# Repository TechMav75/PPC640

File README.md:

# Replacement keyboard controller for an Amstrad PPC640 luggable

The Keyboard Controller directory contain info on converting the existing keyboard to talk USB for use with a modern system. Gerber and schematic files are available in the directory also.

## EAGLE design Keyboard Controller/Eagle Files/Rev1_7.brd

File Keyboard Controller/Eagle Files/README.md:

# Eagle Files

The schematic and board files were created in Eagle v9.0.1

The Gerber files are generated and named for use with http://www.dirtypcbs.com

The board measures out to 4cm x 5.5cm. Can't get it any smaller because of the Teensy++ board.
You will have to use the 10cm x 10cm option, but you can get the proto-pack for $25 shipped

If ANYONE else wants to do the same type of conversion, I have spare boards I'd be will to part with for the cost of shipping. The protopack I ordered came with 12 boards.

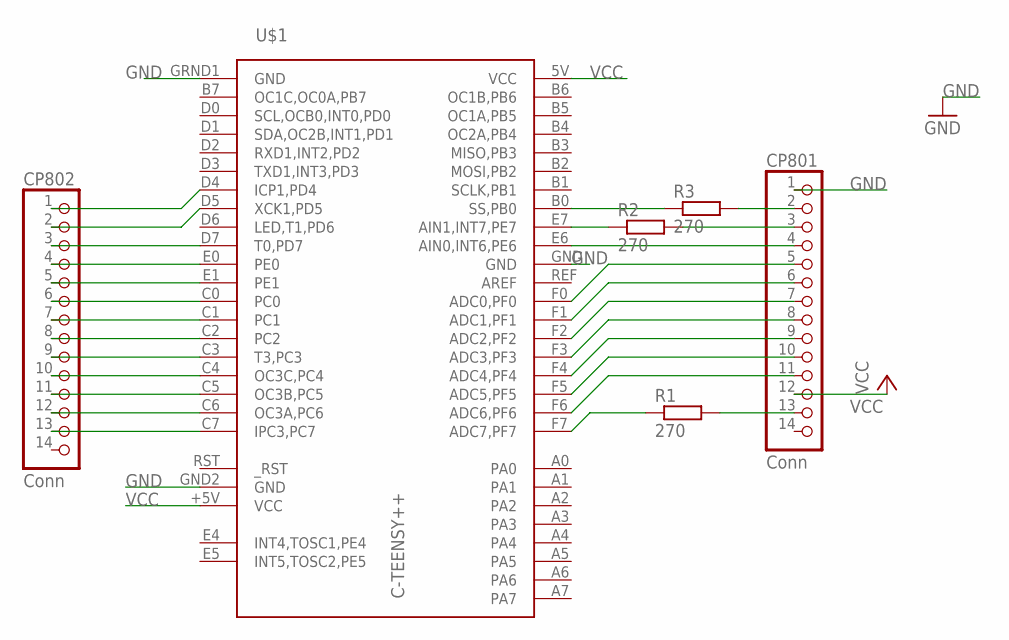
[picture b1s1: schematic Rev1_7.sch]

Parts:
CP801, CP802: Conn; 1X14
R1, R2, R3: 270; R0805
U$1: C-TEENSY++; TEENSY++

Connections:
GND: CP801.1, U$1.GND, U$1.GND2 (GND), U$1.GRND1 (GND)
unnamed: CP801.11, U$1.F6 (ADC6,PF6)
unnamed: CP802.13, U$1.C7 (IPC3,PC7)
unnamed: CP801.10, U$1.F5 (ADC5,PF5)
unnamed: CP801.9, U$1.F4 (ADC4,PF4)
unnamed: CP801.8, U$1.F3 (ADC3,PF3)
unnamed: CP801.7, U$1.F2 (ADC2,PF2)
unnamed: CP801.6, U$1.F1 (ADC1,PF1)
unnamed: CP801.5, U$1.F0 (ADC0,PF0)
unnamed: CP801.4, U$1.E6 (AIN0,INT6,PE6)
unnamed: CP802.12, U$1.C6 (OC3A,PC6)
unnamed: CP802.11, U$1.C5 (OC3B,PC5)
unnamed: CP802.10, U$1.C4 (OC3C,PC4)
unnamed: CP802.9, U$1.C3 (T3,PC3)
unnamed: CP802.8, U$1.C2
unnamed: CP802.7, U$1.C1
unnamed: CP802.6, U$1.C0
unnamed: CP802.5, U$1.E1
unnamed: CP802.4, U$1.E0
unnamed: CP802.3, U$1.D7 (T0,PD7)
unnamed: CP802.2, U$1.D5 (XCK1,PD5)
unnamed: CP802.1, U$1.D4 (ICP1,PD4)
unnamed: CP801.3, R2.2
unnamed: R2.1, U$1.E7 (AIN1,INT7,PE7)
unnamed: R3.1, U$1.B0 (SS,PB0)
unnamed: CP801.2, R3.2
unnamed: R1.1, U$1.F7 (ADC7,PF7)
unnamed: CP801.13, R1.2
VCC: CP801.12, U$1.5V (VCC), U$1.+5V (VCC)

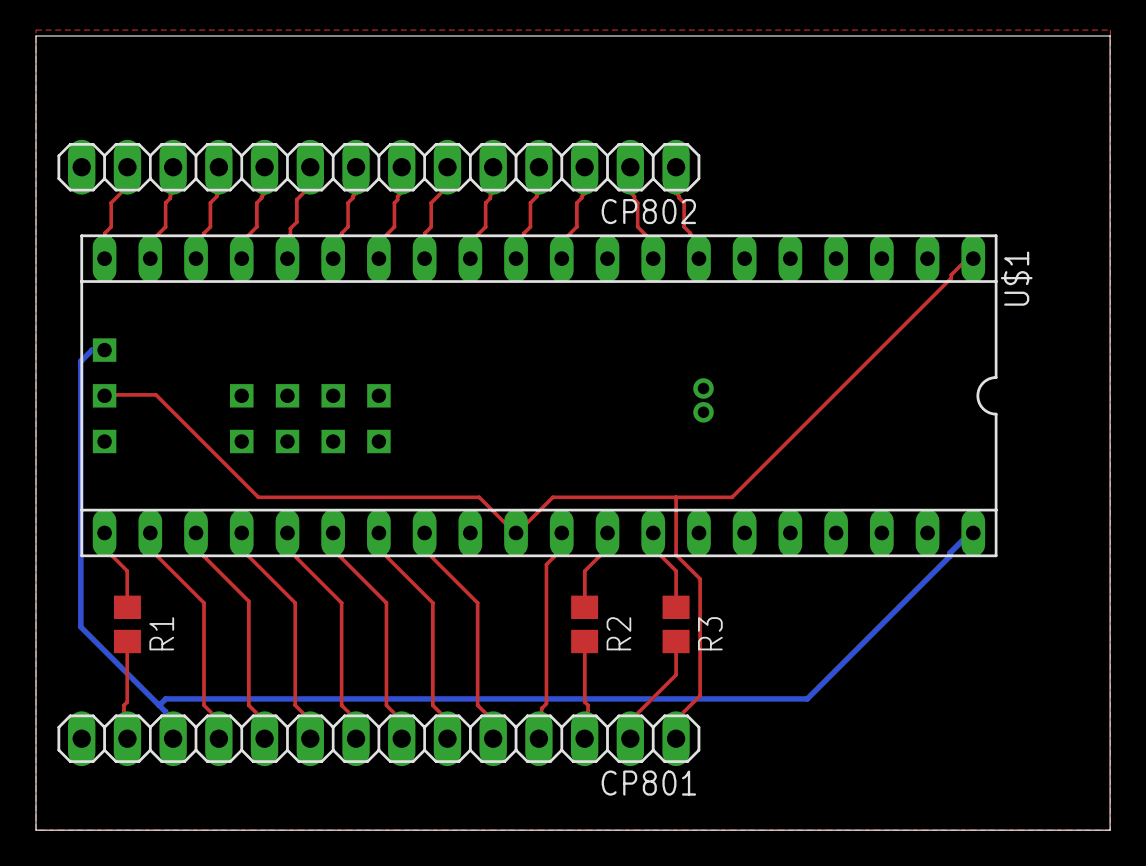
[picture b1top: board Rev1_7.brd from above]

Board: 2 copper layers, 59.7 x 44.1 mm, 6 parts (0 on the bottom side), 29 nets.

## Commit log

2018-05-15 Moving files
2018-05-15 Added Keyboard Map
2018-05-15 Added generic text document for misc info
2018-05-28 Update PPC640.sc
    Regenerated matrix to match new PCB layout
2018-05-29 Create Pinouts
2018-05-29 Added pin assignment breakdown for the Teensy and ribbon cables
2018-05-29 Added Gerber and schematic files
2018-05-29 Added Readme,md file
2018-06-29 Had resistor on wrong pin.
2018-06-29 MOved text to proper layer for silk screen
2018-06-30 Added BOM for board
